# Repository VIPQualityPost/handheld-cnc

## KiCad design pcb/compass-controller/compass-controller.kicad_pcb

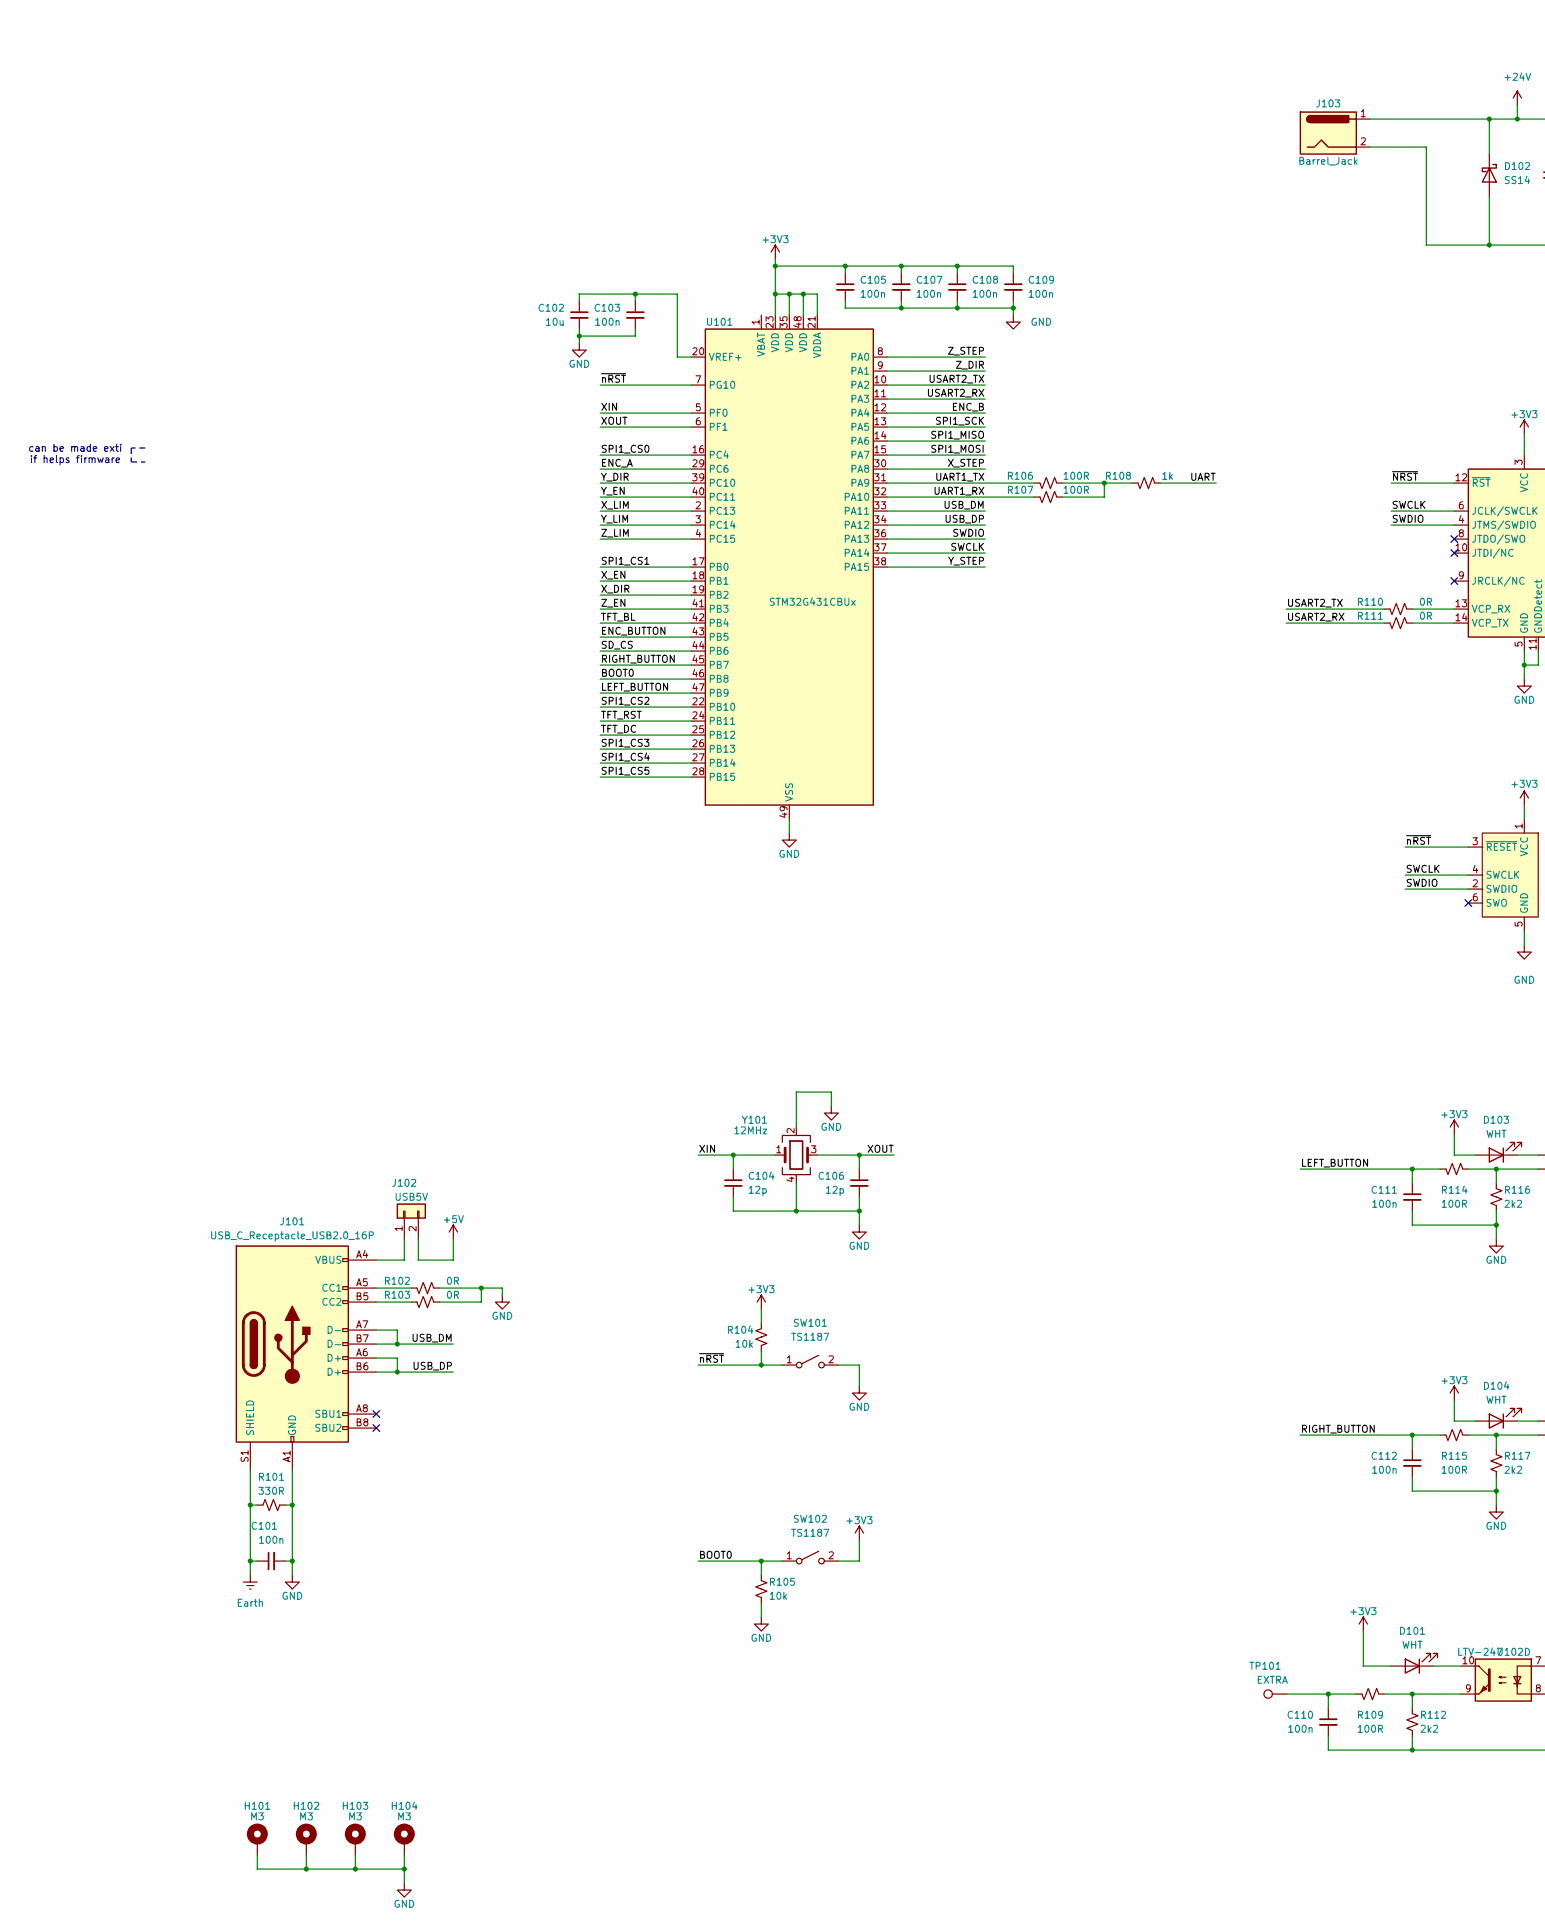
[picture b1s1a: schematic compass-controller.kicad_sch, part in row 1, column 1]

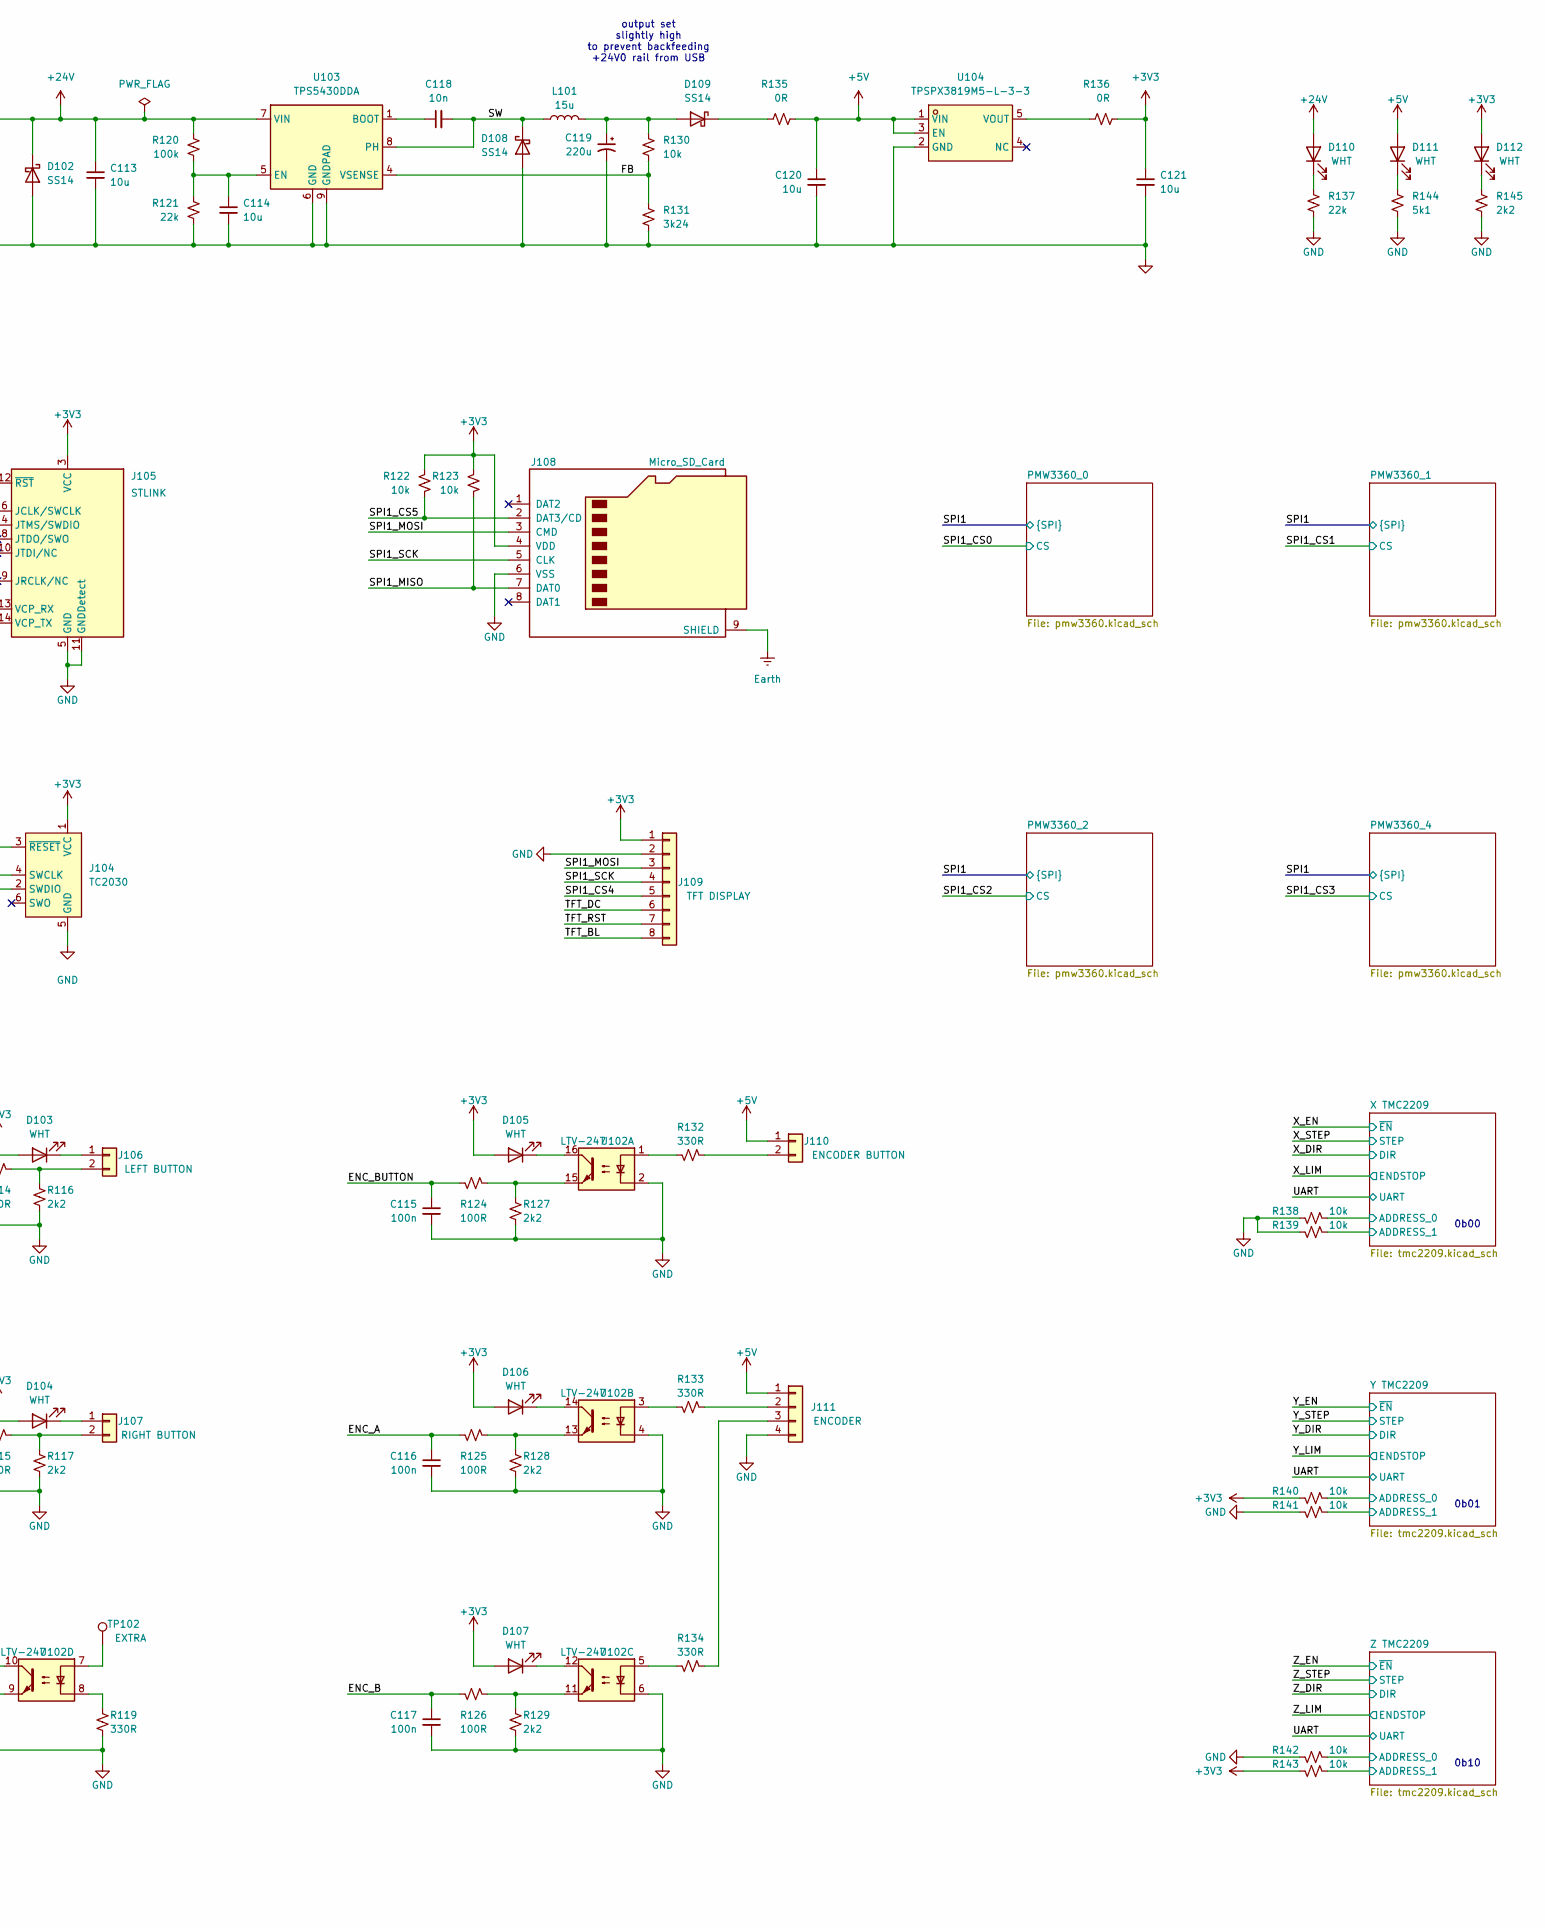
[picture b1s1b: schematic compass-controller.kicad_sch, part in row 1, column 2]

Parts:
C101, C103, C105, C107, C108, C109, C110, C111, C112, C115, C116, C117: 100n; C_0603_1608Metric
C102: 10u; C_1206_3216Metric
C104, C106: 12p; C_0402_1005Metric
C113, C120, C121: 10u; C_1206_3216Metric; LCSC ID C13585
C114: 10u; C_1206_3216Metric; LCSC ID C15849
C118: 10n; C_0402_1005Metric; LCSC ID C15195
C119: 220u; CP_Elec_5x5.4; LCSC ID C18221491
D101, D103, D104, D105, D106, D107, D110, D111, D112: WHT; D_0603_1608Metric
D102, D108, D109: SS14; D_SMA; LCSC ID C2480
H101, H102, H103, H104: M3; MountingHole_3.2mm_M3_DIN965_Pad
J101: USB_C_Receptacle_USB2.0_16P; USB_C_Receptacle_GCT_USB4105-xx-A_16P_TopMnt_Horizontal
J102: USB5V; PinHeader_1x02_P2.54mm_Vertical
J103: Barrel_Jack; BarrelJack_GCT_DCJ200-10-A_Horizontal
J104: TC2030; Tag-Connect_TC2030-IDC-FP_2x03_P1.27mm_Vertical
J105: STLINK; PinHeader_2x07_P1.27mm_Vertical_SMD
J106: LEFT BUTTON; JST_XH_B2B-XH-A_1x02_P2.50mm_Vertical
J107: RIGHT BUTTON; JST_XH_B2B-XH-A_1x02_P2.50mm_Vertical
J108: Micro_SD_Card; microSD_HC_Molex_104031-0811
J109: TFT DISPLAY; GC9A01Round1.28
J110: ENCODER BUTTON; JST_XH_B2B-XH-A_1x02_P2.50mm_Vertical
J111: ENCODER; JST_XH_B4B-XH-A_1x04_P2.50mm_Vertical
L101: 15u; L_Cenker_CKCS8040; LCSC ID C16853
R101, R119, R132, R133, R134: 330R; R_0603_1608Metric
R102, R103, R110, R111, R135, R136: 0R; R_0603_1608Metric
R104, R105, R122, R123, R138, R139, R140, R141, R142, R143: 10k; R_0603_1608Metric
R106, R107, R109, R114, R115, R124, R125, R126: 100R; R_0603_1608Metric
R108: 1k; R_0603_1608Metric
R112, R116, R117, R127, R128, R129, R145: 2k2; R_0603_1608Metric
R120: 100k; R_0603_1608Metric; LCSC ID C14675
R121: 22k; R_0603_1608Metric; LCSC ID C14675
R130: 10k; R_0603_1608Metric; LCSC ID C25804
R131: 3k24; R_0603_1608Metric; LCSC ID C22994
R137: 22k; R_0603_1608Metric
R144: 5k1; R_0603_1608Metric
SW101, SW102: TS1187; SW-SMD_4P-L5.1-W5.1-P3.70-LS6.5-TL_H1.5
TP101, TP102: EXTRA; TestPoint_Pad_D1.5mm
U101: STM32G431CBUx; QFN-48-1EP_7x7mm_P0.5mm_EP5.6x5.6mm
U102: LTV-247; SOP-16_4.4x10.4mm_P1.27mm
U103: TPS5430DDA; TI_SO-PowerPAD-8_ThermalVias; LCSC ID C9864
U104: TPSPX3819M5-L-3-3; SOT-23-5_L3.0-W1.6-P0.95-LS2.8-BR; LCSC Part C5370980
Y101: 12MHz; Crystal_SMD_SeikoEpson_TSX3225-4Pin_3.2x2.5mm

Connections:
+3V3: C105.1, C107.1, C108.1, C109.1, C121.1, D101.2 (A), D103.2 (A), D104.2 (A), D105.2 (A), D106.2 (A), D107.2 (A), D112.2 (A), J104.1 (VCC), J105.3 (VCC), J108.4 (VDD), J109.1, R104.1, R122.1, R123.1, R136.2, R140.1, R143.1, SW102.2 (B), U101.21 (VDDA), U101.23 (VDD), U101.35 (VDD), U101.48 (VDD); also elsewhere on the board
+5V: C120.1, D111.2 (A), J102.2, J110.1, J111.1, R135.2, U104.1 (VIN), U104.3 (EN)
+24V: C113.1, D102.1 (K), D110.2 (A), J103.1, R120.1, U103.7 (VIN)
/BOOT0: R105.1, SW102.1 (A), U101.46 (PB8)
/ENC_A: C116.1, R125.1, U101.29 (PC6)
/ENC_B: C117.1, R126.1, U101.12 (PA4)
/ENC_BUTTON: C115.1, R124.1, U101.43 (PB5)
/FB: R130.2, R131.1, U103.4 (VSENSE)
/LEFT_BUTTON: C111.1, R114.1, U101.47 (PB9)
/RIGHT_BUTTON: C112.1, R115.1, U101.45 (PB7)
/SD_CS: U101.44 (PB6)
/SPI1_CS0: U101.16 (PC4); also elsewhere on the board
/SPI1_CS1: U101.17 (PB0); also elsewhere on the board
/SPI1_CS2: U101.22 (PB10); also elsewhere on the board
/SPI1_CS3: U101.26 (PB13); also elsewhere on the board
/SPI1_CS4: J109.5, U101.27 (PB14)
/SPI1_CS5: J108.2 (DAT3/CD), R122.2, U101.28 (PB15)
/SPI1_MISO: J108.7 (DAT0), R123.2, U101.14 (PA6)
/SPI1_MOSI: J108.3 (CMD), J109.3, U101.15 (PA7)
/SPI1_SCK: J108.5 (CLK), J109.4, U101.13 (PA5)
/SW: C118.2, D108.1 (K), L101.1, U103.8 (PH)
/SWCLK: J104.4 (SWCLK), J105.6 (JCLK/SWCLK), U101.37 (PA14)
/SWDIO: J104.2 (SWDIO), J105.4 (JTMS/SWDIO), U101.36 (PA13)
/TFT_BL: J109.8, U101.42 (PB4)
/TFT_DC: J109.6, U101.25 (PB12)
/TFT_RST: J109.7, U101.24 (PB11)
/UART: R108.2; also elsewhere on the board
/UART1_RX: R107.1, U101.32 (PA10)
/UART1_TX: R106.1, U101.31 (PA9)
/USART2_RX: R111.1, U101.11 (PA3)
/USART2_TX: R110.1, U101.10 (PA2)
/USB_DM: J101.A7 (D-), J101.B7 (D-), U101.33 (PA11)
/USB_DP: J101.A6 (D+), J101.B6 (D+), U101.34 (PA12)
/X TMC2209/ADDRESS_0: R138.2; also elsewhere on the board
/X TMC2209/ADDRESS_1: R139.2; also elsewhere on the board
/XIN: C104.1, U101.5 (PF0), Y101.1
/XOUT: C106.1, U101.6 (PF1), Y101.3
/X_DIR: U101.19 (PB2); also elsewhere on the board
/X_EN: U101.18 (PB1); also elsewhere on the board
/X_LIM: U101.2 (PC13); also elsewhere on the board
/X_STEP: U101.30 (PA8); also elsewhere on the board
/Y TMC2209/ADDRESS_0: R140.2; also elsewhere on the board
/Y TMC2209/ADDRESS_1: R141.2; also elsewhere on the board
/Y_DIR: U101.39 (PC10); also elsewhere on the board
/Y_EN: U101.40 (PC11); also elsewhere on the board
/Y_LIM: U101.3 (PC14); also elsewhere on the board
/Y_STEP: U101.38 (PA15); also elsewhere on the board
/Z TMC2209/ADDRESS_0: R142.2; also elsewhere on the board
/Z TMC2209/ADDRESS_1: R143.2; also elsewhere on the board
/Z_DIR: U101.9 (PA1); also elsewhere on the board
/Z_EN: U101.41 (PB3); also elsewhere on the board
/Z_LIM: U101.4 (PC15); also elsewhere on the board
/Z_STEP: U101.8 (PA0); also elsewhere on the board
/~NRST: J105.12 (~RST)
/~nRST: J104.3 (~RESET), R104.2, SW101.1 (A), U101.7 (PG10)
Earth: C101.1, J101.S1 (SHIELD), J108.9 (SHIELD), R101.1
GND: C101.2, C102.2, C103.2, C104.2, C105.2, C106.2, C107.2, C108.2, C109.2, C110.2, C111.2, C112.2, C113.2, C114.2, C115.2, C116.2, C117.2, C119.2, C120.2, C121.2, D102.2 (A), D108.2 (A), H101.1, H102.1, H103.1, H104.1, J101.A1 (GND), J101.A12 (GND), J101.B1 (GND), J101.B12 (GND), J103.2, J104.5 (GND), J105.5 (GND), J105.7 (GND), J105.11 (GNDDetect), J108.6 (VSS), J109.2, J111.4, R101.2, R102.2, R103.2, R105.2, R112.2, R116.2, R117.2, R119.2, R121.2, R127.2, R128.2, R129.2, R131.2, R137.2, R138.1, R139.1, R141.1, R142.1, R144.2, R145.2, SW101.2 (B), U101.49 (VSS), U102.2, U102.4, U102.6, U103.6 (GND), U103.9 (GNDPAD), U104.2 (GND), Y101.2, Y101.4; also elsewhere on the board
unnamed: C110.1, R109.1, TP101.1
unnamed: D101.1 (K), U102.10
unnamed: D103.1 (K), J106.1
unnamed: D104.1 (K), J107.1
unnamed: D105.1 (K), U102.16
unnamed: D106.1 (K), U102.14
unnamed: D107.1 (K), U102.12
unnamed: C119.1, D109.2 (A), L101.2, R130.1
unnamed: D109.1 (K), R135.1
unnamed: D110.1 (K), R137.1
unnamed: D111.1 (K), R144.1
unnamed: D112.1 (K), R145.1
unnamed: J101.A5 (CC1), R102.1
unnamed: J101.B5 (CC2), R103.1
unnamed: J101.A4 (VBUS), J101.A9 (VBUS), J101.B4 (VBUS), J101.B9 (VBUS), J102.1
unnamed: J105.13 (VCP_RX), R110.2
unnamed: J105.14 (VCP_TX), R111.2
unnamed: J106.2, R114.2, R116.1
unnamed: J107.2, R115.2, R117.1
unnamed: J110.2, R132.2
unnamed: J111.2, R133.2
unnamed: J111.3, R134.2
unnamed: R106.2, R107.2, R108.1
unnamed: R109.2, R112.1, U102.9
unnamed: R119.1, U102.8
unnamed: R124.2, R127.1, U102.15
unnamed: R125.2, R128.1, U102.13
unnamed: R126.2, R129.1, U102.11
unnamed: R132.1, U102.1
unnamed: R133.1, U102.3
unnamed: R134.1, U102.5
unnamed: TP102.1, U102.7
unnamed: C102.1, C103.1, U101.20 (VREF+)
unnamed: C118.1, U103.1 (BOOT)
unnamed: C114.1, R120.2, R121.1, U103.5 (EN)
unnamed: R136.1, U104.5 (VOUT)

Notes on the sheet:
0b00
can be made exti if helps firmware
0b01
output set slightly high to prevent backfeeding +24V0 rail from USB
0b10

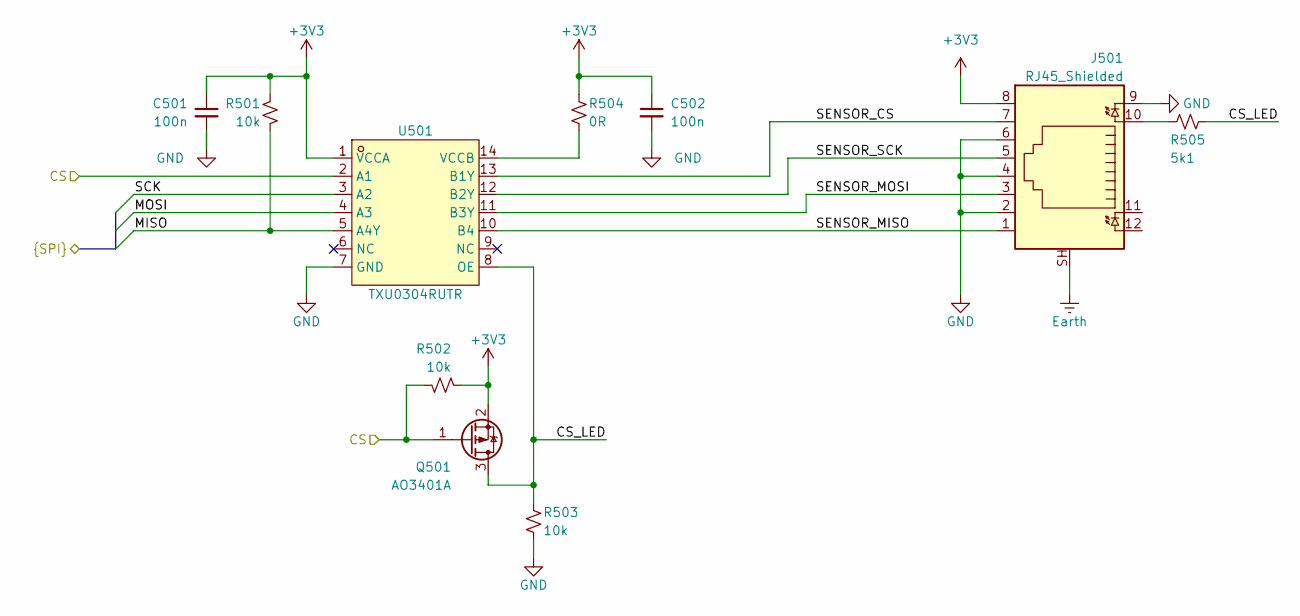
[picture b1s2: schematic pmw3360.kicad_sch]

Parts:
C501, C502: 100n; C_0603_1608Metric
J501: RJ45_Shielded; RJ45-TH_HR915310A
Q501: AO3401A; SOT-23
R501, R502, R503: 10k; R_0603_1608Metric
R504: 0R; R_0603_1608Metric
R505: 5k1; R_0603_1608Metric
U501: TXU0304RUTR; TSSOP-14_4.4x5mm_P0.65mm; LCSC Part C4364118

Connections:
+3V3: C501.1, C502.1, J501.8, Q501.2 (S), R501.1, R502.2, R504.1, U501.1 (VCCA); also elsewhere on the board
/PMW3360_4/CS_LED: Q501.3 (D), R503.1, R505.2, U501.8 (OE)
/PMW3360_4/MISO: R501.2, U501.5 (A4Y)
/PMW3360_4/MOSI: U501.4 (A3)
/PMW3360_4/SCK: U501.3 (A2)
/PMW3360_4/SENSOR_CS: J501.7, U501.13 (B1Y)
/PMW3360_4/SENSOR_MISO: J501.1, U501.10 (B4)
/PMW3360_4/SENSOR_MOSI: J501.3, U501.11 (B3Y)
/PMW3360_4/SENSOR_SCK: J501.5, U501.12 (B2Y)
/SPI1_CS3: Q501.1 (G), R502.1, U501.2 (A1); also elsewhere on the board
GND: C501.2, C502.2, J501.2, J501.4, J501.6, J501.9, R503.2, U501.7 (GND); also elsewhere on the board
unnamed: J501.10, R505.1
unnamed: R504.2, U501.14 (VCCB)

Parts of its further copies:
C601, C602, C701, C702, C801, C802: 100n; C_0603_1608Metric
J601, J701, J801: RJ45_Shielded; RJ45-TH_HR915310A
Q601, Q701, Q801: AO3401A; SOT-23
R601, R602, R603, R701, R702, R703, R801, R802, R803: 10k; R_0603_1608Metric
R604, R704, R804: 0R; R_0603_1608Metric
R605, R705, R805: 5k1; R_0603_1608Metric
U601, U701, U801: TXU0304RUTR; TSSOP-14_4.4x5mm_P0.65mm; LCSC Part C4364118

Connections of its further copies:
+3V3: C601.1, C602.1, C701.1, C702.1, C801.1, C802.1, J601.8, J701.8, J801.8, Q601.2 (S), Q701.2 (S), Q801.2 (S), R601.1, R602.2, R604.1, R701.1, R702.2, R704.1, R801.1, R802.2, R804.1, U601.1 (VCCA), U701.1 (VCCA), U801.1 (VCCA); also elsewhere on the board
/PMW3360_0/CS_LED: Q801.3 (D), R803.1, R805.2, U801.8 (OE)
/PMW3360_0/MISO: R801.2, U801.5 (A4Y)
/PMW3360_0/MOSI: U801.4 (A3)
/PMW3360_0/SCK: U801.3 (A2)
/PMW3360_0/SENSOR_CS: J801.7, U801.13 (B1Y)
/PMW3360_0/SENSOR_MISO: J801.1, U801.10 (B4)
/PMW3360_0/SENSOR_MOSI: J801.3, U801.11 (B3Y)
/PMW3360_0/SENSOR_SCK: J801.5, U801.12 (B2Y)
/PMW3360_1/CS_LED: Q701.3 (D), R703.1, R705.2, U701.8 (OE)
/PMW3360_1/MISO: R701.2, U701.5 (A4Y)
/PMW3360_1/MOSI: U701.4 (A3)
/PMW3360_1/SCK: U701.3 (A2)
/PMW3360_1/SENSOR_CS: J701.7, U701.13 (B1Y)
/PMW3360_1/SENSOR_MISO: J701.1, U701.10 (B4)
/PMW3360_1/SENSOR_MOSI: J701.3, U701.11 (B3Y)
/PMW3360_1/SENSOR_SCK: J701.5, U701.12 (B2Y)
/PMW3360_2/CS_LED: Q601.3 (D), R603.1, R605.2, U601.8 (OE)
/PMW3360_2/MISO: R601.2, U601.5 (A4Y)
/PMW3360_2/MOSI: U601.4 (A3)
/PMW3360_2/SCK: U601.3 (A2)
/PMW3360_2/SENSOR_CS: J601.7, U601.13 (B1Y)
/PMW3360_2/SENSOR_MISO: J601.1, U601.10 (B4)
/PMW3360_2/SENSOR_MOSI: J601.3, U601.11 (B3Y)
/PMW3360_2/SENSOR_SCK: J601.5, U601.12 (B2Y)
/SPI1_CS0: Q801.1 (G), R802.1, U801.2 (A1); also elsewhere on the board
/SPI1_CS1: Q701.1 (G), R702.1, U701.2 (A1); also elsewhere on the board
/SPI1_CS2: Q601.1 (G), R602.1, U601.2 (A1); also elsewhere on the board
GND: C601.2, C602.2, C701.2, C702.2, C801.2, C802.2, J601.2, J601.4, J601.6, J601.9, J701.2, J701.4, J701.6, J701.9, J801.2, J801.4, J801.6, J801.9, R603.2, R703.2, R803.2, U601.7 (GND), U701.7 (GND), U801.7 (GND); also elsewhere on the board
unnamed: J601.10, R605.1
unnamed: J701.10, R705.1
unnamed: J801.10, R805.1
unnamed: R604.2, U601.14 (VCCB)
unnamed: R704.2, U701.14 (VCCB)
unnamed: R804.2, U801.14 (VCCB)

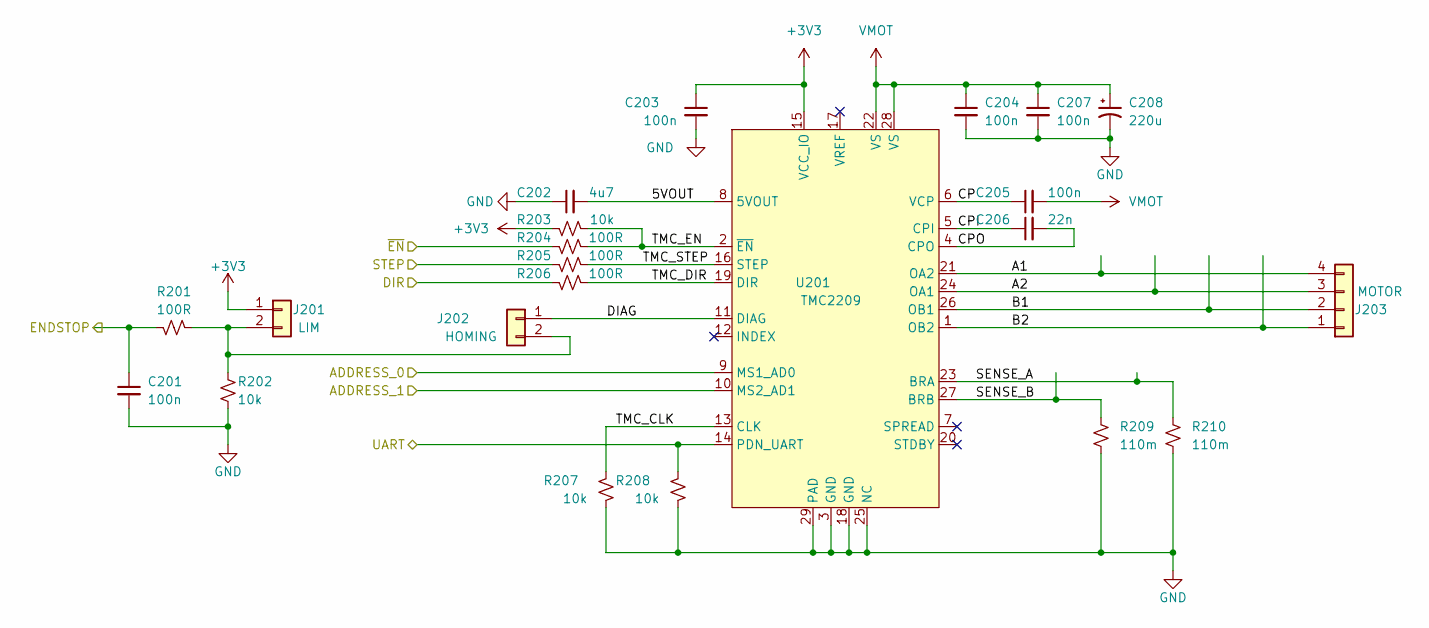
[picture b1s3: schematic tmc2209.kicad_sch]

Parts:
C201, C203, C204, C205, C207: 100n; C_0603_1608Metric
C202: 4u7; C_0603_1608Metric
C206: 22n; C_0402_1005Metric
C208: 220u; CP_Elec_5x5.4
J201: LIM; JST_XH_B2B-XH-A_1x02_P2.50mm_Vertical
J202: HOMING; PinHeader_2x01_P2.54mm_Vertical
J203: MOTOR; JST_XH_B4B-XH-AM_1x04_P2.50mm_Vertical
R201, R204, R205, R206: 100R; R_0603_1608Metric
R202, R203, R207, R208: 10k; R_0603_1608Metric
R209, R210: 110m; R_2512_6332Metric
U201: TMC2209; QFN-28-1EP_5x5mm_P0.5mm_EP3.75x3.75mm

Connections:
+3V3: C203.1, J201.1, R203.1, U201.15 (VCC_IO); also elsewhere on the board
/UART: R208.1, U201.14 (PDN_UART); also elsewhere on the board
/X TMC2209/5VOUT: C202.2, U201.8 (5VOUT)
/X TMC2209/A1: J203.4, U201.21 (OA2)
/X TMC2209/A2: J203.3, U201.24 (OA1)
/X TMC2209/ADDRESS_0: U201.9 (MS1_AD0); also elsewhere on the board
/X TMC2209/ADDRESS_1: U201.10 (MS2_AD1); also elsewhere on the board
/X TMC2209/B1: J203.2, U201.26 (OB1)
/X TMC2209/B2: J203.1, U201.1 (OB2)
/X TMC2209/CP: C205.1, U201.6 (VCP)
/X TMC2209/CPI: C206.1, U201.5 (CPI)
/X TMC2209/CPO: C206.2, U201.4 (CPO)
/X TMC2209/DIAG: J202.1, U201.11 (DIAG)
/X TMC2209/SENSE_A: R210.1, U201.23 (BRA)
/X TMC2209/SENSE_B: R209.1, U201.27 (BRB)
/X TMC2209/TMC_CLK: R207.1, U201.13 (CLK)
/X TMC2209/TMC_DIR: R206.2, U201.19 (DIR)
/X TMC2209/TMC_EN: R203.2, R204.2, U201.2 (~EN)
/X TMC2209/TMC_STEP: R205.2, U201.16 (STEP)
/X_DIR: R206.1; also elsewhere on the board
/X_EN: R204.1; also elsewhere on the board
/X_LIM: C201.1, R201.1; also elsewhere on the board
/X_STEP: R205.1; also elsewhere on the board
GND: C201.2, C202.1, C203.2, C204.2, C207.2, C208.2, R202.2, R207.2, R208.2, R209.2, R210.2, U201.3 (GND), U201.18 (GND), U201.25 (NC), U201.29 (PAD); also elsewhere on the board
unnamed: J201.2, J202.2, R201.2, R202.1
VMOT: C204.1, C205.2, C207.1, C208.1, U201.22 (VS), U201.28 (VS); also elsewhere on the board

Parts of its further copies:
C301, C303, C304, C305, C307, C401, C403, C404, C405, C407: 100n; C_0603_1608Metric
C302, C402: 4u7; C_0603_1608Metric
C306, C406: 22n; C_0402_1005Metric
C308, C408: 220u; CP_Elec_5x5.4
J301, J401: LIM; JST_XH_B2B-XH-A_1x02_P2.50mm_Vertical
J302, J402: HOMING; PinHeader_2x01_P2.54mm_Vertical
J303, J403: MOTOR; JST_XH_B4B-XH-AM_1x04_P2.50mm_Vertical
R301, R304, R305, R306, R401, R404, R405, R406: 100R; R_0603_1608Metric
R302, R303, R307, R308, R402, R403, R407, R408: 10k; R_0603_1608Metric
R309, R310, R409, R410: 110m; R_2512_6332Metric
U301, U401: TMC2209; QFN-28-1EP_5x5mm_P0.5mm_EP3.75x3.75mm

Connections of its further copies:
+3V3: C303.1, C403.1, J301.1, J401.1, R303.1, R403.1, U301.15 (VCC_IO), U401.15 (VCC_IO); also elsewhere on the board
/UART: R308.1, R408.1, U301.14 (PDN_UART), U401.14 (PDN_UART); also elsewhere on the board
/Y TMC2209/5VOUT: C302.2, U301.8 (5VOUT)
/Y TMC2209/A1: J303.4, U301.21 (OA2)
/Y TMC2209/A2: J303.3, U301.24 (OA1)
/Y TMC2209/ADDRESS_0: U301.9 (MS1_AD0); also elsewhere on the board
/Y TMC2209/ADDRESS_1: U301.10 (MS2_AD1); also elsewhere on the board
/Y TMC2209/B1: J303.2, U301.26 (OB1)
/Y TMC2209/B2: J303.1, U301.1 (OB2)
/Y TMC2209/CP: C305.1, U301.6 (VCP)
/Y TMC2209/CPI: C306.1, U301.5 (CPI)
/Y TMC2209/CPO: C306.2, U301.4 (CPO)
/Y TMC2209/DIAG: J302.1, U301.11 (DIAG)
/Y TMC2209/SENSE_A: R310.1, U301.23 (BRA)
/Y TMC2209/SENSE_B: R309.1, U301.27 (BRB)
/Y TMC2209/TMC_CLK: R307.1, U301.13 (CLK)
/Y TMC2209/TMC_DIR: R306.2, U301.19 (DIR)
/Y TMC2209/TMC_EN: R303.2, R304.2, U301.2 (~EN)
/Y TMC2209/TMC_STEP: R305.2, U301.16 (STEP)
/Y_DIR: R306.1; also elsewhere on the board
/Y_EN: R304.1; also elsewhere on the board
/Y_LIM: C301.1, R301.1; also elsewhere on the board
/Y_STEP: R305.1; also elsewhere on the board
/Z TMC2209/5VOUT: C402.2, U401.8 (5VOUT)
/Z TMC2209/A1: J403.4, U401.21 (OA2)
/Z TMC2209/A2: J403.3, U401.24 (OA1)
/Z TMC2209/ADDRESS_0: U401.9 (MS1_AD0); also elsewhere on the board
/Z TMC2209/ADDRESS_1: U401.10 (MS2_AD1); also elsewhere on the board
/Z TMC2209/B1: J403.2, U401.26 (OB1)
/Z TMC2209/B2: J403.1, U401.1 (OB2)
/Z TMC2209/CP: C405.1, U401.6 (VCP)
/Z TMC2209/CPI: C406.1, U401.5 (CPI)
/Z TMC2209/CPO: C406.2, U401.4 (CPO)
/Z TMC2209/DIAG: J402.1, U401.11 (DIAG)
/Z TMC2209/SENSE_A: R410.1, U401.23 (BRA)
/Z TMC2209/SENSE_B: R409.1, U401.27 (BRB)
/Z TMC2209/TMC_CLK: R407.1, U401.13 (CLK)
/Z TMC2209/TMC_DIR: R406.2, U401.19 (DIR)
/Z TMC2209/TMC_EN: R403.2, R404.2, U401.2 (~EN)
/Z TMC2209/TMC_STEP: R405.2, U401.16 (STEP)
/Z_DIR: R406.1; also elsewhere on the board
/Z_EN: R404.1; also elsewhere on the board
/Z_LIM: C401.1, R401.1; also elsewhere on the board
/Z_STEP: R405.1; also elsewhere on the board
GND: C301.2, C302.1, C303.2, C304.2, C307.2, C308.2, C401.2, C402.1, C403.2, C404.2, C407.2, C408.2, R302.2, R307.2, R308.2, R309.2, R310.2, R402.2, R407.2, R408.2, R409.2, R410.2, U301.3 (GND), U301.18 (GND), U301.25 (NC), U301.29 (PAD), U401.3 (GND), U401.18 (GND), U401.25 (NC), U401.29 (PAD); also elsewhere on the board
unnamed: J301.2, J302.2, R301.2, R302.1
unnamed: J401.2, J402.2, R401.2, R402.1
VMOT: C304.1, C305.2, C307.1, C308.1, C404.1, C405.2, C407.1, C408.1, U301.22 (VS), U301.28 (VS), U401.22 (VS), U401.28 (VS); also elsewhere on the board

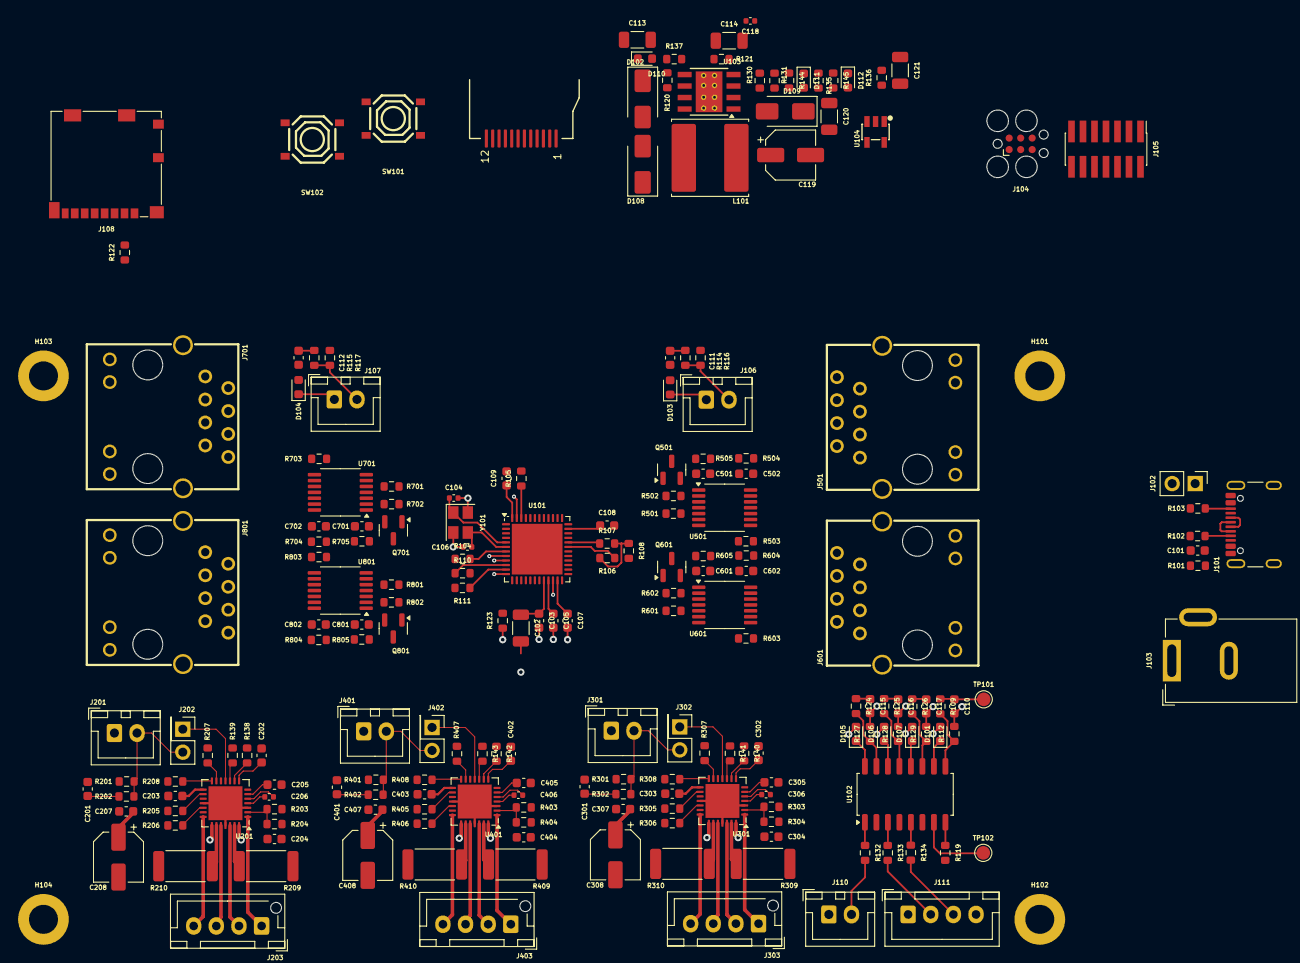
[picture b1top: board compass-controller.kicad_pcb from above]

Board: 4 copper layers, 207 parts (0 on the bottom side), 172 nets.

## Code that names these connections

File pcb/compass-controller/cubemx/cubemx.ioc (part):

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Mcu.Name=STM32G431C(6-8-B)Ux
Mcu.Package=UFQFPN48
Mcu.UserName=STM32G431CBUx
PA0.GPIOParameters=GPIO_Label
PA0.GPIO_Label=Z_STEP
PA0.Signal=S_TIM2_CH1
PA1.GPIOParameters=GPIO_Label
PA1.GPIO_Label=Z_DIR
PA1.Signal=GPIO_Output
PA10.GPIOParameters=GPIO_Label
PA10.GPIO_Label=TMC_RX
PA10.Mode=Asynchronous
PA10.Signal=USART1_RX
PA11.Mode=Device
PA11.Signal=USB_DM
PA12.Mode=Device
PA12.Signal=USB_DP
PA13.Mode=Serial_Wire
PA13.Signal=SYS_JTMS-SWDIO
PA14.Mode=Serial_Wire
PA14.Signal=SYS_JTCK-SWCLK
PA15.GPIOParameters=GPIO_Label
PA15.GPIO_Label=Y_STEP
PA15.Signal=S_TIM8_CH1
PA2.Mode=Asynchronous
PA2.Signal=USART2_TX
PA3.Mode=Asynchronous
PA3.Signal=USART2_RX
PA4.GPIOParameters=GPIO_Label
PA4.GPIO_Label=ENC_B
PA4.Signal=S_TIM3_CH2
PA5.GPIOParameters=GPIO_Label
PA5.GPIO_Label=PMW_SCK
PA5.Mode=Full_Duplex_Master
PA5.Signal=SPI1_SCK
PA6.GPIOParameters=GPIO_Label
PA6.GPIO_Label=PMW_MISO
PA6.Mode=Full_Duplex_Master
PA6.Signal=SPI1_MISO
PA7.GPIOParameters=GPIO_Label
PA7.GPIO_Label=PMW_MOSI
PA7.Mode=Full_Duplex_Master
PA7.Signal=SPI1_MOSI
PA8.GPIOParameters=GPIO_Label
PA8.GPIO_Label=X_STEP
PA8.Signal=S_TIM1_CH1
PA9.GPIOParameters=GPIO_Label
PA9.GPIO_Label=TMC_TX
PA9.Mode=Asynchronous
PA9.Signal=USART1_TX
PB0.GPIOParameters=GPIO_Label
PB0.GPIO_Label=MPW_MUX1
PB0.Signal=GPIO_Output
PB1.GPIOParameters=GPIO_Label
PB1.GPIO_Label=X_EN
PB1.Signal=GPIO_Output
PB10.GPIOParameters=GPIO_Label
PB10.GPIO_Label=TFT_CS
PB10.Signal=GPIO_Output
PB11.GPIOParameters=GPIO_Label
PB11.GPIO_Label=TFT_RST
PB11.Signal=GPIO_Output
PB12.GPIOParameters=GPIO_Label
PB12.GPIO_Label=TFT_DC
PB12.Signal=GPIO_Output
PB13.GPIOParameters=GPIO_Label
PB13.GPIO_Label=TFT_SCK
PB13.Mode=Full_Duplex_Master
PB13.Signal=SPI2_SCK
PB14.GPIOParameters=GPIO_Label
PB14.GPIO_Label=TFT_MISO
PB14.Mode=Full_Duplex_Master
PB14.Signal=SPI2_MISO
PB15.GPIOParameters=GPIO_Label
PB15.GPIO_Label=TFT_MOSI
PB15.Mode=Full_Duplex_Master
PB15.Signal=SPI2_MOSI
PB2.GPIOParameters=GPIO_Label
PB2.GPIO_Label=X_DIR
PB2.Signal=GPIO_Output
PB3.GPIOParameters=GPIO_Label
PB3.GPIO_Label=Z_EN
PB3.Signal=GPIO_Output
PB4.GPIOParameters=GPIO_Label
PB4.GPIO_Label=TFT_BL
PB4.Signal=S_TIM16_CH1
PB5.GPIOParameters=GPIO_Label
PB5.GPIO_Label=ENCODER_BUTTON
PB5.Signal=GPIO_Input
PB6.GPIOParameters=GPIO_Label
PB6.GPIO_Label=SD_CS
PB6.Signal=GPIO_Output
PB7.GPIOParameters=GPIO_Label
PB7.GPIO_Label=RIGHT_BUTTON
PB7.Signal=GPIO_Input
PB8-BOOT0.GPIOParameters=GPIO_Label
PB8-BOOT0.GPIO_Label=BOOT0
PB8-BOOT0.Signal=GPIO_Input
PB9.GPIOParameters=GPIO_Label
PB9.GPIO_Label=LEFT_BUTTON
PB9.Signal=GPIO_Input
PC10.GPIOParameters=GPIO_Label
PC10.GPIO_Label=Y_DIR
PC10.Signal=GPIO_Output
PC11.GPIOParameters=GPIO_Label
PC11.GPIO_Label=Y_EN
PC11.Signal=GPIO_Output
PC13.GPIOParameters=GPIO_Label
PC13.GPIO_Label=X_LIM
PC13.Signal=GPIO_Input
PC14-OSC32_IN.GPIOParameters=GPIO_Label
PC14-OSC32_IN.GPIO_Label=Y_LIM
PC14-OSC32_IN.Signal=GPIO_Input
PC15-OSC32_OUT.GPIOParameters=GPIO_Label
PC15-OSC32_OUT.GPIO_Label=Z_LIM
PC15-OSC32_OUT.Signal=GPIO_Input
PC4.GPIOParameters=GPIO_Label
PC4.GPIO_Label=PWM_MUX0
PC4.Signal=GPIO_Output
PC6.GPIOParameters=GPIO_Label
PC6.GPIO_Label=ENC_A
PC6.Signal=S_TIM3_CH1
PF0-OSC_IN.Mode=HSE-External-Oscillator
PF0-OSC_IN.Signal=RCC_OSC_IN
PF1-OSC_OUT.Mode=HSE-External-Oscillator
PF1-OSC_OUT.Signal=RCC_OSC_OUT
PG10-NRST.GPIOParameters=GPIO_Label
PG10-NRST.GPIO_Label=nRESET
PG10-NRST.Signal=GPIO_Input
RCC.HSE_VALUE=12000000
RCC.SYSCLKFreq_VALUE=168000000
RCC.SYSCLKSource=RCC_SYSCLKSOURCE_PLLCLK
board=custom

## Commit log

2025-07-25 work on controller
2025-07-25 build platform
2025-07-27 get stm32 project building, start on hardware encoder support
2025-07-28 get working teensy + stm32g4 build
2025-07-28 update pinout to support SD card
2025-07-29 work on schematic
2025-08-01 finalize schematic, add footprints, start layout
2025-09-06 work on layout
